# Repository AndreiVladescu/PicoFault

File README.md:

# PicoFault

PicoFault is a compact, low-cost Electromagnetic Fault Injection tool designed for hobby and academic research.

PicoFault is a remix of [FaultyCat](https://github.com/ElectronicCats/faultycat) by Electronic Cats, which is itself a remix of [ChipSHOUTER PicoEMP](https://github.com/newaetech/chipshouter-picoemp) by Colin O'Flynn. Design changes in PicoFault are focused on a smaller form factor, improved BOM availability, and lower cost of production.

This project is built in KiCad. Tested before release, but it is a product that must be handled with care — please read the instructions for use.

**IMPORTANT**: The plastic shield is critical for safe operation. While the output itself is isolated from the input connections, you will still **easily shock yourself** on the exposed high-voltage capacitor and circuitry. **NEVER** operate the device without the shield.

**WARNING**: The high voltage will be applied across the SMA connector. If an injection tip (coil) is present, it will absorb most of the power. If you leave the SMA connector open, you will present a high voltage pulse across this SMA and could shock yourself. Do NOT touch the output SMA tip as a general best practice, and treat the output as if it has a high voltage present at all times.

## Features

- Voltage glitching
- Trigger using dedicated pins
- Trigger voltage reference for more accurate glitch timing
- Analog input to monitor target device status during glitching
- JTAG/SWD scanner

## Programming PicoFault

Follow the bootloader mode steps in the wiki to program the device. You can run other tasks on the microcontroller as well.

## Useful References

If you are new to Electromagnetic Fault Injection (EMFI), a couple of chapters of the Hardware Hacking Handbook are a good starting point. You can also find a practical demo of PicoEMP used in a real attack in the TI CC SimpleLink attack demo.

## Contributors

PicoFault stands on the shoulders of:

- Colin O'Flynn — original ChipSHOUTER PicoEMP hardware design and Python demo
- Electronic Cats — FaultyCat redesign, KiCad port, BOM modifications
- stacksmashing — C firmware for full PIO feature set
- Lennert Wouters — C improvements, first real attack demo
- @nilswiersma — triggering and C improvements

## License

PicoFault is adapted from FaultyCat by Electronic Cats, which is adapted from ChipSHOUTER PicoEMP by Colin O'Flynn. This project is licensed under **Creative Commons Attribution-ShareAlike 3.0 Unported (CC BY-SA 3.0)**.

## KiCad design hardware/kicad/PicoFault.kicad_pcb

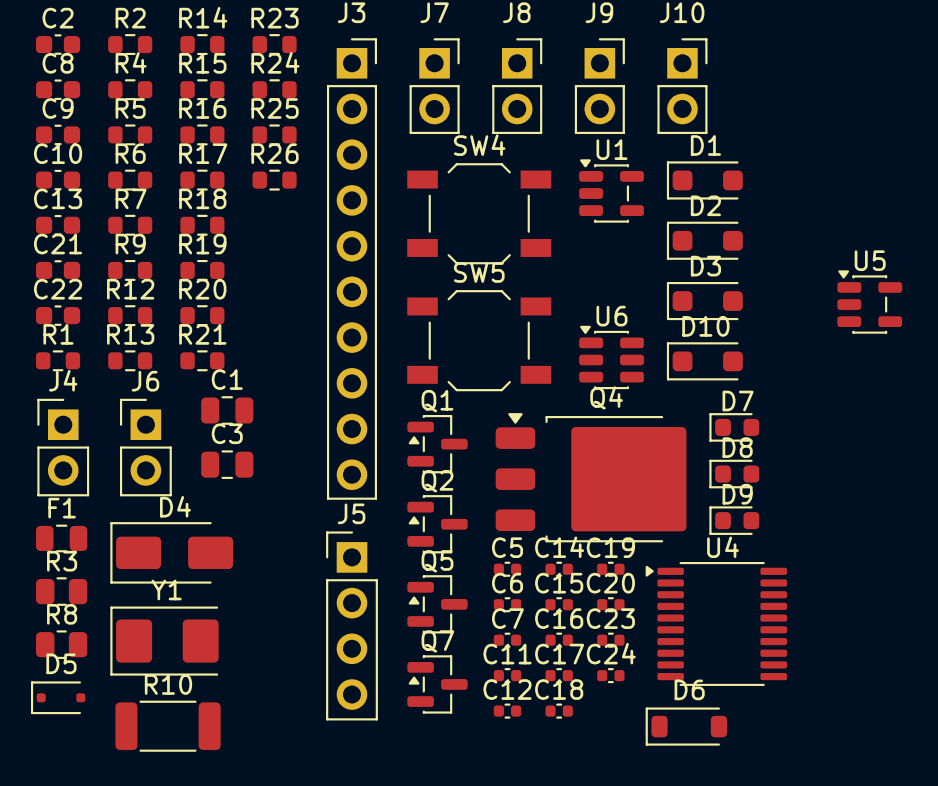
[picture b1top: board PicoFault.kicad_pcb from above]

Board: 2 copper layers, 78 parts (0 on the bottom side), 43 nets, no tracks yet.

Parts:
C1, C3: 4.7uF; C_0805_2012Metric
C2, C21, C22: 100nF; C_0603_1608Metric
C5, C6, C23, C24: 10uF; C_0402_1005Metric
C7, C11, C12, C14, C15, C16, C17, C18, C19, C20: 100nF; C_0402_1005Metric
C8, C10: 27pF; C_0603_1608Metric
C9, C13: 1uF; C_0603_1608Metric
D1, D2, D3, D10: SM4005PL-TP; D_SOD-123F
D4: MURA160T3G; D_SMA
D5: MM3Zxx; D_SOD-323F
D6: MBR120; D_SOD-123
D7: H.V.Detected; LED_0603_1608Metric
D8: Status; LED_0603_1608Metric
D9: Charge On; LED_0603_1608Metric
F1: 0.5A; Fuse_0805_2012Metric
J3: Conn_01x10; PinSocket_1x10_P2.54mm_Vertical
J4: Header 2; PinHeader_1x02_P2.54mm_Vertical
J5: Header 4; PinHeader_1x04_P2.54mm_Vertical
J6: Input Power:2x AA Battery; PinHeader_1x02_P2.54mm_Vertical
J7: GLITCHER_EN; PinSocket_1x02_P2.54mm_Vertical
J8: ANALOG_PINS; PinSocket_1x02_P2.54mm_Vertical
J9: TRIGGER_IN; PinSocket_1x02_P2.54mm_Vertical
J10: TRIGGER_VREF; PinSocket_1x02_P2.54mm_Vertical
Q1, Q2: AO3422; SOT-23
Q4: RGT16BM65DTL; TO-252-3_TabPin2
Q5: DMG3415U-7; SOT-23
Q7: IRLML2502; SOT-23
R1, R9: 10R; R_0603_1608Metric
R2, R4: 5.1K; R_0603_1608Metric
R3: 75R; R_0805_2012Metric
R5, R6, R13, R14, R16: 1K; R_0603_1608Metric
R7: 22K; R_0603_1608Metric
R8: 2K; R_0805_2012Metric
R10: 20M; R_2010_5025Metric
R12: 100K; R_0603_1608Metric
R15: 4.7k; R_0603_1608Metric
R17, R25, R26: 10K; R_0603_1608Metric
R18: 1k; R_0603_1608Metric
R19, R20: 27; R_0603_1608Metric
R21: 10k; R_0603_1608Metric
R23, R24: 1R; R_0603_1608Metric
SW4: RESET; SW_SPST_TL3342
SW5: BOOT; SW_SPST_TL3342
U1: AP2112K-3.3; SOT-23-5
U4: TXS0108EPW; TSSOP-20_4.4x6.5mm_P0.65mm
U5: TLV75718PDBV; SOT-23-5
U6: SN74LVC1T45DBV; SOT-23-6
Y1: 12Mhz; Crystal_SMD_5032-2Pin_5.0x3.2mm

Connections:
+1V2: C9.1, C11.1, C12.1
+1V8: C23.1, U5.5 (OUT)
+3V3: C6.1, C7.1, C13.1, C14.1, C15.1, C16.1, C17.1, C18.1, C19.1, C20.1, C21.2, D1.2 (A), J5.2, R7.1, R17.1, U1.5 (VOUT), U4.19 (VCCB), U6.1 (VCCA)
/ANALOG: J8.1, J8.2
/CHARGED: J5.1, R7.2
/GLITCHER: J7.1, J7.2, Q7.3 (D)
/HVPULSE: D2.2 (A), J4.2
/HVPWM: D3.2 (A), J5.4
/QSPI_CS: R17.2, SW5.2
/TRIGGER_IN: J9.1, J9.2, U6.4 (B)
/TRIGGER_VREF: J10.1, J10.2, U6.6 (VCCB)
/VIN: C5.1, C24.1, U1.1 (VIN), U1.3 (EN), U5.1 (IN), U5.3 (EN)
/VREFOUT: C22.1, R15.1, U4.2 (VCCA)
/VSYS: D10.1 (K), Q5.3 (D)
GND: C1.2, C2.2, C3.2, C5.2, C6.2, C7.2, C8.2, C9.2, C10.2, C11.2, C12.2, C13.2, C14.2, C15.2, C16.2, C17.2, C18.2, C19.2, C20.2, C21.1, C22.2, C23.2, C24.2, D7.1 (K), D8.1 (K), D9.1 (K), J3.10, J4.1, J5.3, J6.2, Q1.2 (S), Q2.2 (S), Q7.2 (S), R2.2, R4.2, R5.2, R6.2, R12.2, R21.1, R25.2, R26.1, SW4.1, SW5.1, U1.2 (GND), U4.11 (GND), U5.2 (GND), U6.2 (GND)
unnamed: C10.1, R18.1, Y1.2
unnamed: D1.1 (K), R1.1, R3.1
unnamed: D2.1 (K), Q2.1 (G), R5.1
unnamed: D3.1 (K), Q1.1 (G), R6.1
unnamed: D5.2 (A), Q4.2, R8.2
unnamed: D5.1 (K), Q4.1, R9.2
unnamed: D6.1 (K), Q5.2 (S)
unnamed: D7.2 (A), R13.1
unnamed: D8.2 (A), R14.1
unnamed: D9.2 (A), R16.2
unnamed: D10.2 (A), J6.1
unnamed: J3.2, U4.1 (A1)
unnamed: J3.3, U4.3 (A2)
unnamed: J3.4, U4.4 (A3)
unnamed: J3.5, U4.5 (A4)
unnamed: J3.6, U4.6 (A5)
unnamed: J3.7, U4.7 (A6)
unnamed: J3.8, U4.8 (A7)
unnamed: J3.9, U4.9 (A8)
unnamed: Q7.1 (G), R23.1, R25.1
unnamed: R24.2, R26.2
unnamed: C2.1, R1.2
unnamed: R8.1, R9.1
unnamed: C1.1, C3.1, R3.2
unnamed: C8.1, Y1.1
unnamed: R15.2, U4.10 (OE)
unnamed: R21.2, U6.5 (DIR)
VBUS: D6.2 (A), F1.2, Q5.1 (G), R12.1

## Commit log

2026-05-19 KiCAD initial commit
2026-05-19 Minor touch-ups
